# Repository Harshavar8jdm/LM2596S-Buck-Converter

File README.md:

# LM2596S-Buck-Converter
Custom LM2596S Buck Converter

## Hardware Visuals

### PCB Layout

### 3D Renders
| Front Render | Back Render |
| :---: | :---: |
|  |  |

### Schematic

---

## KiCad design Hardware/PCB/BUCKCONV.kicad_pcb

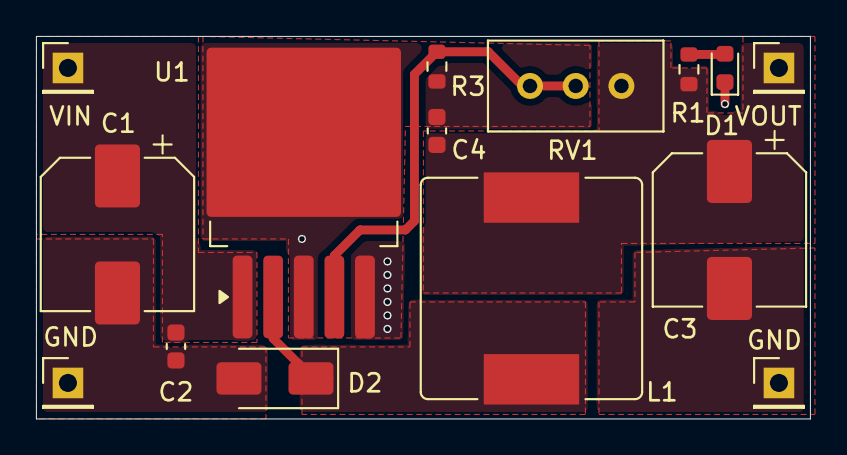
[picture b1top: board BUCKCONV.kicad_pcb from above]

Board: 2 copper layers, 43.0 x 21.2 mm, 15 parts (0 on the bottom side), 6 nets.

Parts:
C1: 100uF; CP_Elec_8x10
C2, C4: 100nF; C_0603_1608Metric
C3: 220uF; CP_Elec_8x10
D1: LED; LED_0603_1608Metric
D2: SS34; D_SMA
GND: Conn_01x01_Pin; PinHeader_1x01_P2.54mm_Vertical
GND#2: Conn_01x01_Pin; PinHeader_1x01_P2.54mm_Vertical
L1: 47uH; L_Bourns_SRR1210A
R1: 4K7; R_0603_1608Metric
R3: 1K; R_0603_1608Metric
RV1: R_Potentiometer; Potentiometer_Bourns_3296W_Vertical
U1: LM2596S-ADJ; TO-263-5_TabPin3
VIN: Conn_01x01_Pin; PinHeader_1x01_P2.54mm_Vertical
VOUT: Conn_01x01_Pin; PinHeader_1x01_P2.54mm_Vertical

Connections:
/SW: D2.1 (K), L1.1, U1.2 (OUT)
/VIN: C1.1, C2.1, U1.1 (VIN), VIN.1
/VOUT: C3.1, C4.1, L1.2, R1.1, RV1.1, VOUT.1
GND: C1.2, C2.2, C3.2, C4.2, D1.1 (K), D2.2 (A), GND.1, GND#2.1, R3.2, U1.3 (GND), U1.5 (~ON/OFF)
unnamed: D1.2 (A), R1.2
unnamed: R3.1, RV1.2, RV1.3, U1.4 (FB)
